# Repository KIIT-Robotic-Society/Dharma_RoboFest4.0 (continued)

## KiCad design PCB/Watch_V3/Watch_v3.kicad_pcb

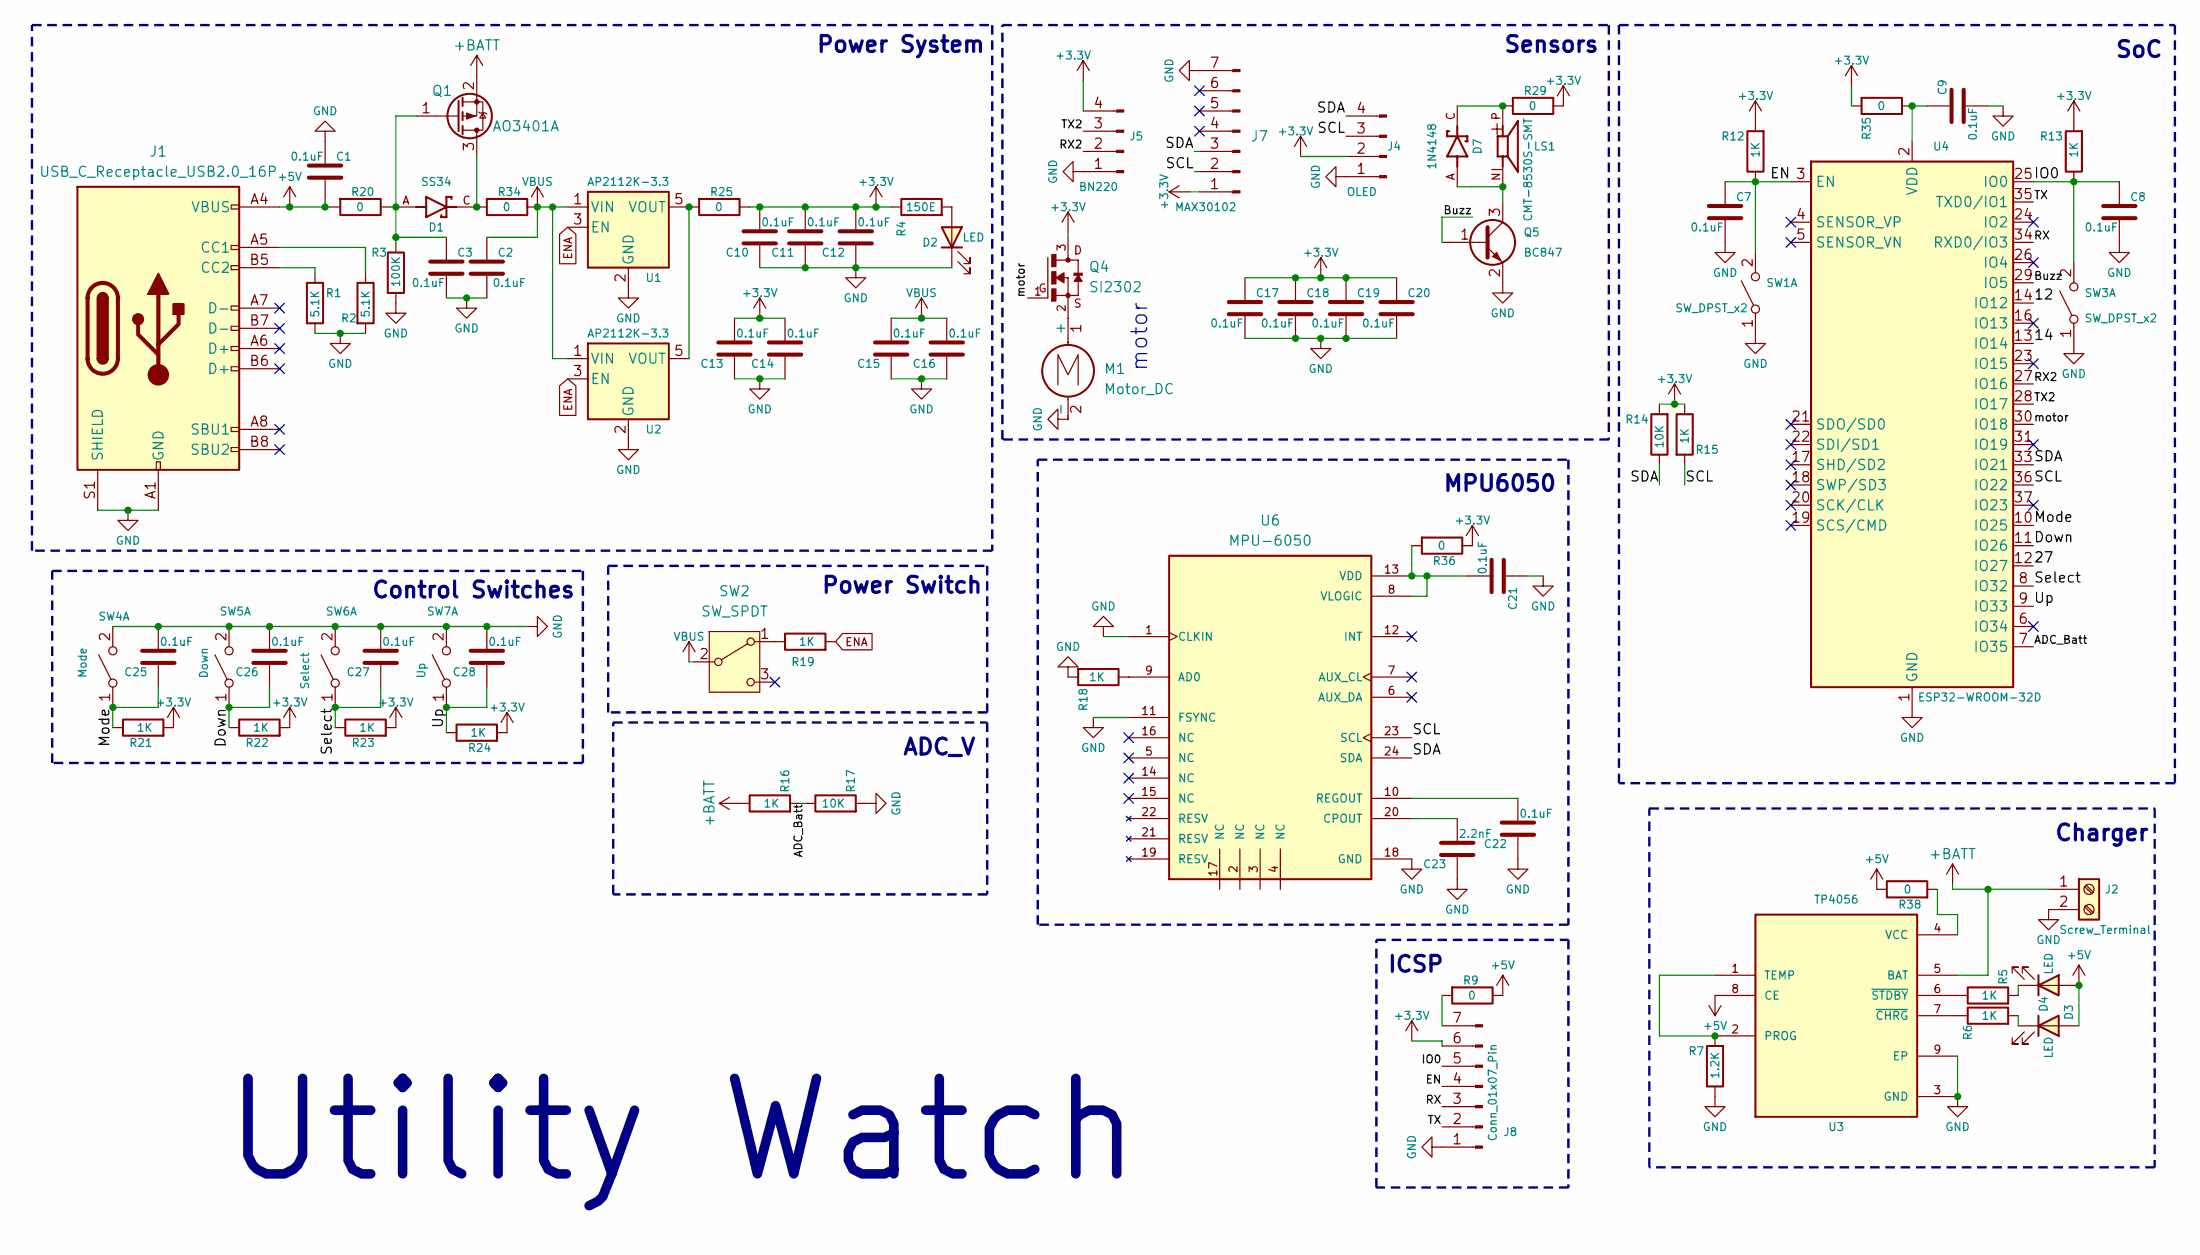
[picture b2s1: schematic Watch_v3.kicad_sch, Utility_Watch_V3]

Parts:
C1, C2, C3, C7, C8, C9, C10, C11, C12, C13, C14, C15, C16, C17, C18, C19, C20, C21, C22, C25, C26, C27, C28: 0.1uF; C_0402_1005Metric
C23: 2.2nF; C_0402_1005Metric
D1: SS34; P25_DO-214AC_SMA; PARTREV 31 Aug 2016
D2, D3, D4: LED; LED_0402_1005Metric
D7: 1N4148; D_SOD-323; PARTREV 31 Aug 2016
J1: USB_C_Receptacle_USB2.0_16P; USB_C_Receptacle_GCT_USB4105-xx-A_16P_TopMnt_Horizontal
J2: Screw_Terminal; solder_pad_batt
J4: OLED; PinHeader_1x04_P2.54mm_Vertical
J5: BN220; solder_pad_4
J7: MAX30102; PinHeader_1x07_P2.54mm_Vertical
J8: Conn_01x07_Pin; solder_7
LS1: CMT-8530S-SMT; CUI_CMT-8530S-SMT
M1: Motor_DC; solder_motor
Q1: AO3401A; SOT-23
Q4: SI2302; SOT23
Q5: BC847; SOT-23
R1, R2: 5.1K; R_0402_1005Metric
R3: 100K; R_0402_1005Metric
R4: 150E; R_0402_1005Metric
R5, R6, R12, R13, R15, R16, R18, R19, R21, R22, R23, R24: 1K; R_0402_1005Metric
R7: 1.2K; R_0402_1005Metric
R9, R20, R25, R29, R34, R35, R36, R38: 0; R_0402_1005Metric
R14, R17: 10K; R_0402_1005Metric
SW1, SW3: SW_DPST_x2; SW_SPST_B3U-1000P-B
SW2: SW_SPDT; SW_Slide_1P2T_CK_OS102011MS2Q
SW4: Mode; SW_Tactile_SPST_NO_Straight_CK_PTS636Sx25SMTRLFS
SW5: Down; SW_Tactile_SPST_NO_Straight_CK_PTS636Sx25SMTRLFS
SW6: Select; SW_Tactile_SPST_NO_Straight_CK_PTS636Sx25SMTRLFS
SW7: Up; SW_Tactile_SPST_NO_Straight_CK_PTS636Sx25SMTRLFS
U1, U2: AP2112K-3.3; SOT-23-5
U3: TP4056; HSOP-8-1EP_3.9x4.9mm_P1.27mm_EP2.3x2.3mm
U4: ESP32-WROOM-32D
U6: MPU-6050; QFN-24-1EP_3x3mm_P0.4mm_EP1.75x1.6mm; PARTREV 3.4

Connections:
+3.3V: C10.1, C11.1, C12.1, C13.1, C14.1, C17.2, C18.2, C19.2, C20.2, J4.2, J5.4, J7.1, J8.6, Q4.3, R4.1, R12.2, R13.2, R14.2, R15.1, R21.2, R22.2, R23.2, R24.2, R25.1, R29.1, R35.2, R36.1
+5V: C1.1, D3.2 (A), D4.2 (A), J1.A4 (VBUS), J1.A9 (VBUS), J1.B4 (VBUS), J1.B9 (VBUS), R9.1, R20.2, R38.1, U3.8 (CE)
+BATT: J2.1, Q1.2 (S), R16.1, U3.5 (BAT)
/12: U4.14 (IO12)
/14: U4.13 (IO14)
/27: U4.12 (IO27)
/ADC_Batt: R16.2, R17.1, U4.7 (IO35)
/Buzz: Q5.1 (B), U4.29 (IO5)
/Down: C26.2, R22.1, SW5.1 (A), U4.11 (IO26)
/EN: C7.2, J8.4, R12.1, SW1.2 (B), U4.3 (EN)
/IO0: C8.2, J8.5, R13.1, SW3.2 (B), U4.25 (IO0)
/Mode: C25.2, R21.1, SW4.1 (A), U4.10 (IO25)
/RX: J8.3, U4.34 (RXD0/IO3)
/RX2: J5.2, U4.27 (IO16)
/SCL: J4.3, J7.2, R15.2, U4.36 (IO22), U6.23 (SCL)
/SDA: J4.4, J7.3, R14.1, U4.33 (IO21), U6.24 (SDA)
/Select: C27.2, R23.1, SW6.1 (A), U4.8 (IO32)
/TX: J8.2, U4.35 (TXD0/IO1)
/TX2: J5.3, U4.28 (IO17)
/Up: C28.2, R24.1, SW7.1 (A), U4.9 (IO33)
/motor: Q4.1, U4.30 (IO18)
ENA: R19.2, U1.3 (EN), U2.3 (EN)
GND: C1.2, C2.1, C3.1, C7.1, C8.1, C9.1, C10.2, C11.2, C12.2, C13.2, C14.2, C15.2, C16.2, C17.1, C18.1, C19.1, C20.1, C21.2, C22.2, C23.2, C25.1, C26.1, C27.1, C28.1, D2.1 (K), J1.A1 (GND), J1.A12 (GND), J1.B1 (GND), J1.B12 (GND), J1.S1 (SHIELD), J2.2, J4.1, J5.1, J7.7, J8.1, M1.2 (-), Q5.2 (E), R1.2, R2.2, R3.2, R7.1, R17.2, R18.2, SW1.1 (A), SW3.1 (A), SW4.2 (B), SW5.2 (B), SW6.2 (B), SW7.2 (B), U1.2 (GND), U2.2 (GND), U3.3 (GND), U3.9 (EP), U4.1 (GND), U4.15 (GND), U4.38 (GND), U4.39 (GND), U6.1 (CLKIN), U6.11 (FSYNC), U6.18 (GND)
unnamed: D2.2 (A), R4.2
unnamed: D3.1 (K), R5.2
unnamed: D4.1 (K), R6.2
unnamed: D7.C, LS1.P, R29.2
unnamed: J1.A5 (CC1), R2.1
unnamed: J1.B5 (CC2), R1.1
unnamed: J8.7, R9.2
unnamed: M1.1 (+), Q4.2
unnamed: D1.C, Q1.3 (D), R34.2
unnamed: C3.2, D1.A, Q1.1 (G), R3.1, R20.1
unnamed: D7.A, LS1.N, Q5.3 (C)
unnamed: R19.1, SW2.1 (A)
unnamed: R25.2, U1.5 (VOUT), U2.5 (VOUT)
unnamed: R7.2, U3.1 (TEMP), U3.2 (PROG)
unnamed: R38.2, U3.4 (VCC)
unnamed: R6.1, U3.7 (~CHRG)
unnamed: R5.1, U3.6 (~STDBY)
unnamed: C9.2, R35.1, U4.2 (VDD)
unnamed: R18.1, U6.9 (AD0)
unnamed: C23.1, U6.20 (CPOUT)
unnamed: C22.1, U6.10 (REGOUT)
unnamed: C21.1, R36.2, U6.8 (VLOGIC), U6.13 (VDD)
VBUS: C2.2, C15.1, C16.1, R34.1, SW2.2 (B), U1.1 (VIN), U2.1 (VIN)

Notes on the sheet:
MPU6050
motor
Power System
ADC_V
ICSP
SoC
Sensors
Charger
Control Switches
Power Switch
Utility Watch

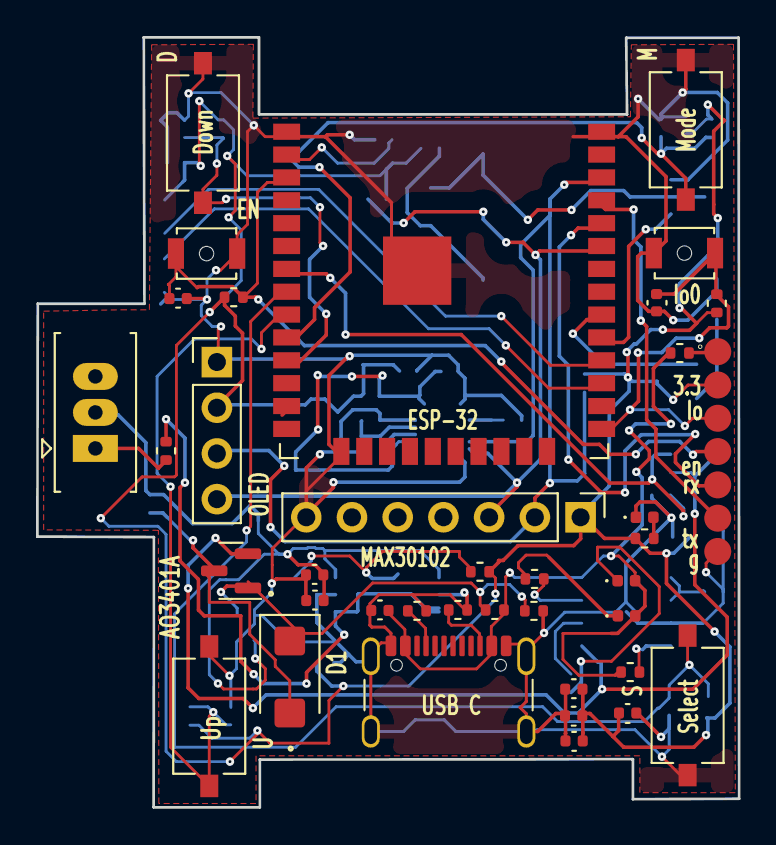
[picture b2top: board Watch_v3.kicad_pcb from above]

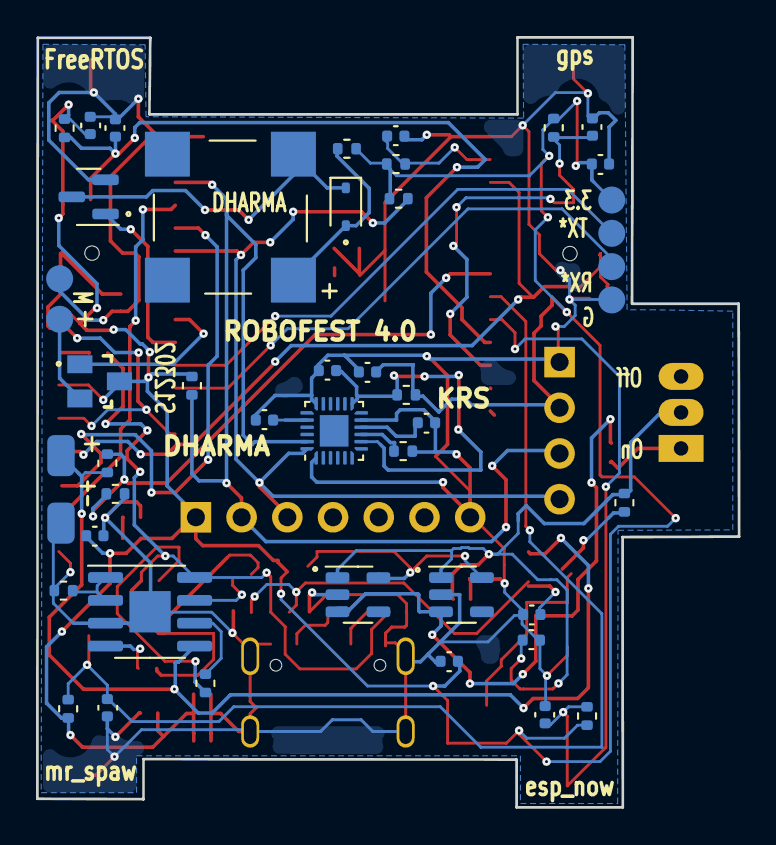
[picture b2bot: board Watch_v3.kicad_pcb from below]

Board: 2 copper layers, 39.0 x 42.8 mm, 79 parts (41 on the bottom side), 43 nets.

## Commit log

2024-11-16 Updating file_name
2024-11-16 Updating folder
2024-11-16 updating folders
2024-11-20 File update
2024-11-20 updating watch_v3
2024-11-21 update PCB_watchV3
2024-11-21 updating PCB_watchV3
2024-11-23 updating watchV3
2024-11-27 remote_v3
2024-11-28 remote_v2 update
2024-11-29 update remote_v2
2024-11-29 update watch_v3
2024-12-05 updating PCBs
2024-12-05 updating PCB design
2025-01-04 updating PCB
2025-01-26 changing README.md file
2025-01-26 updating README.md
2025-01-26 updating ST WorkBench and BLDC configuration and peripheral electronics trial code
2025-01-26 Updating PCB files
2025-01-26 uploading PDF of PCB
2025-01-27 Update LICENSE
2025-02-01 updating files and folders
2025-02-19 changing PCB files
